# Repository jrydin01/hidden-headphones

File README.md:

# Hidden Headphones

> **Bone conduction headphones that sit on your collarbone, completely hidden under your shirt.**

Hidden Headphones is an open-source hardware project for a discrete, neckband-style bone conduction audio device. The electronics sit in a small rear enclosure while flexible wiring runs through the neckband to vibration pads positioned on the collarbone. The goal is a hands-free listening device that can be worn beneath a shirt.

This repository contains the design documentation, KiCad source files, firmware, bill of materials, and OpenSCAD enclosure model for the current prototype revision.

---

## Overview & Architecture

The audio path begins with a phone or computer sending Bluetooth Classic A2DP audio to the original ESP32. The microcontroller outputs stereo PCM audio over I2S to the PCM5102A DAC. Two PAM8302A mono amplifiers drive the left and right bone conduction transducers installed in sealed TPU contact pads.

The project utilizes a custom electronics assembly, dedicated power subsystem, and 3D-printed housing:

* **Core processor:** Original ESP32-WROOM-32 development board with Wi-Fi and Bluetooth Classic
* **Audio input:** Bluetooth A2DP sink running on the ESP32
* **Audio conversion:** PCM5102A stereo I2S DAC
* **Amplification:** Two PAM8302A 2.5 W class-D mono amplifier boards
* **Transducers:** Two 8 ohm, 1 W bone conduction transducers
* **Power:** 3.7 V, 1000 mAh LiPo battery and USB-C TP4056 charging/protection module
* **Controls:** Active-low tactile volume buttons with internal pull-ups
* **Housing:** PETG rear electronics box with flexible TPU neckband sections and sealed contact pads

### Audio and control pins

The current firmware uses the following original ESP32 GPIO assignments:

| Function | GPIO | Notes |
| --- | ---: | --- |
| I2S LRCK / word select | 25 | PCM5102A clock signal |
| I2S BCK / bit clock | 26 | PCM5102A clock signal |
| I2S data out | 22 | PCM5102A serial audio data |
| Volume up | 16 | Active LOW, SW1 |
| Volume down | 17 | Active LOW, SW2 |
| Play/pause | 18 | Active LOW, SW3 |
| Status LED | 19 | LED_STATUS output |

The buttons use a 50 ms software debounce interval. A press changes the Bluetooth sink volume by 10 steps, clamped to the supported range of 0 to 127. The device advertises as **Hidden Headphones**.

## Features

* Hidden collarbone-mounted bone conduction audio
* Wireless Bluetooth A2DP playback
* Stereo output through two independent transducers
* USB-C charging through the TP4056 module
* Dedicated volume up and volume down controls
* Modular rear electronics enclosure
* Flexible cable routing through the neckband
* Open KiCad schematic and PCB source files
* Parametric OpenSCAD enclosure source

## Bill of materials

The complete sourcing list is available in [BOM.csv](BOM.csv). The main assemblies are:

| Category | Part | Quantity |
| --- | --- | ---: |
| Microcontroller | ESP32-WROOM-32 development board | 1 |
| Audio DAC | PCM5102A I2S stereo module | 1 |
| Amplifier | PAM8302A mono amplifier board | 2 |
| Power management | USB-C TP4056 charging and protection module | 1 |
| Battery | 3.7 V 1000 mAh LiPo pack | 1 |
| Audio | Bone conduction transducer, 8 ohm / 1 W | 2 |
| Controls | 6 x 6 x 5 mm tactile push buttons | 3 |
| Hardware | M2 brass heat-set inserts | 4 |
| Wiring | 28 AWG stranded silicone wire | 1 set |
| Printed materials | TPU and PETG filament | 1 spool each |

## Hardware design

The first design phase established the collarbone contact-pad concept, rear electronics box, battery position, and cable route. The second revision reorganized the electronics around dual amplifier channels and added space for the updated power and audio circuitry.

The rear enclosure is modeled in [rear_box.scad](rear_box.scad). Its current design includes:

* A hollow electronics cavity measuring 55 x 30 x 18 mm internally
* A 2 mm nominal wall thickness
* A USB-C charging-port cutout
* Left and right conduit openings for the neckband wiring
* Four internal PCB mounting posts
* M2 screw and heat-set insert locations
* Separate bottom-case and lid modules for 3D printing

The neckband is intended to use flexible TPU sections for comfort and PETG for the more rigid rear enclosure. The contact pads are designed around sealed TPU housings, with cable strain relief and acoustic tuning features considered in the mechanical revision.

## Firmware

The source firmware is available in [firmware.ino](firmware.ino). It uses the Arduino framework and `ESP32-A2DP` to receive Bluetooth audio and route it over I2S to the PCM5102A and PAM8302A amplifiers. It also handles the three active-low controls and status LED shown in the design diagram.

The firmware currently:

1. Starts a Bluetooth A2DP sink named `Hidden Headphones`.
2. Configures the ESP32 I2S output for the PCM5102A.
3. Enables internal pull-ups for the volume and play/pause buttons.
4. Debounces button input and applies software volume scaling.
5. Controls A2DP playback and the status LED with the play/pause button.
6. Reports startup and control changes over the serial monitor at 115200 baud.

The root-level [firmware.ino](firmware.ino) is also retained as a firmware source snapshot. Keep the two copies synchronized when making firmware changes.

### Flashing and verification

1. Install the ESP32 Arduino board support package and the `ESP32-A2DP` library.
2. Select an original ESP32/WROOM-32 board and its USB serial port.
3. Flash `firmware.ino`.
4. Open a serial monitor at 115200 baud.
6. Confirm the `Bluetooth A2DP sink and PCM5102A I2S output ready` message.
7. Pair a phone or computer with **Hidden Headphones** and verify stereo audio, volume, and play/pause controls.

The pin assignments should be checked against the revised PCB before powering the complete system. The selected GPIOs avoid GPIO0 boot strapping and GPIO1 serial TX conflicts on the ESP32-WROOM-32. The PCB must match this mapping before flashing the firmware.

## Repository structure

```text
.
├── BOM.csv                                      # Component list and sourcing links
├── JOURNAL.md                                   # Project development log and time tracking
├── LICENSE                                      # CC0-1.0 license
├── README.md                                    # Project overview and build guide
├── firmware.ino                                 # Root firmware snapshot
├── firmware.ino                                 # ESP32 Bluetooth A2DP firmware
├── rear_box.scad                                # Parametric rear enclosure model
├── Hidden_Headphones_All_Components_v3.kicad_sch # KiCad schematic
├── Hidden_Headphones_All_Components_v3.kicad_pcb # KiCad PCB layout
├── Hidden_Headphones_All_Components_v3.kicad_pro # KiCad project settings
├── images/                                      # Design, CAD, PCB, and firmware images
└── Untitled/                                    # Additional KiCad working files
```

## Project history

The development log in [JOURNAL.md](JOURNAL.md) records the design process and time spent on each stage:

* **Initial concept:** Established the ESP32 audio architecture, collarbone contact pads, TPU housing, and USB-C rechargeable battery system.
* **CAD and assembly:** Designed the rear electronics box, internal mounting layout, cable conduits, and labyrinth-style strain relief.
* **Component sourcing:** Selected the controller, DAC, amplifiers, charging module, battery, transducers, controls, hardware, wiring, and print materials.
* **Architecture revision:** Added dual PAM8302A amplifiers, revised the power system, and documented the antenna keep-out and sealed contact-pad concepts.
* **Housing model:** Completed the main swept and hollowed enclosure and aligned internal hardware mounting points.
* **PCB design:** Created the KiCad schematic and board layout, resolved schematic and footprint issues, and prepared the design for fabrication.
* **Firmware:** Implemented Bluetooth A2DP playback, I2S routing, volume controls, debouncing, serial output, and the flashing verification procedure.

## Current status

The repository represents a prototype design prepared for hardware fabrication and bring-up. The PCB, firmware, and enclosure should be validated together on assembled hardware, especially the power connections, GPIO assignments, amplifier wiring, battery protection, enclosure clearances, and transducer sealing.

This is an experimental hardware project. Use an appropriate LiPo charging module, inspect batteries and wiring for damage, and do not leave the device charging unattended.

---

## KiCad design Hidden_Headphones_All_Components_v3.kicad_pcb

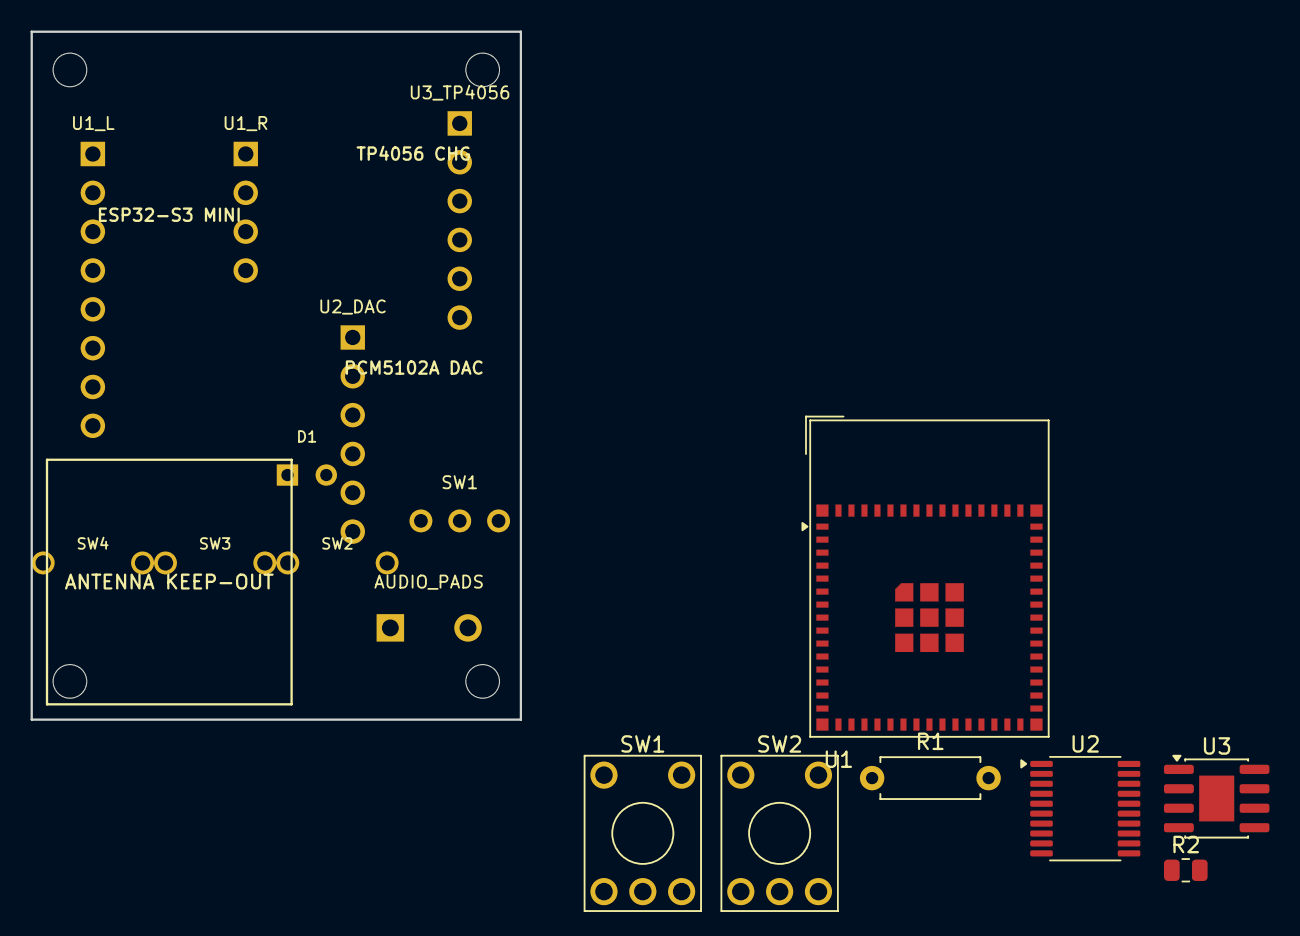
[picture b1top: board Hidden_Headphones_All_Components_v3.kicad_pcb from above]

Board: 2 copper layers, 32.0 x 45.0 mm, 17 parts (0 on the bottom side), 20 nets, no tracks yet.

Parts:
AUDIO_PADS: AUDIO; TerminalBlock_bornier-2_P5.08mm
D1: STATUS; LED_D3.0mm
R1: 1.2kΩ; R_Axial_DIN0207_L6.3mm_D2.5mm_P7.62mm_Horizontal
R2: 10kΩ; R_0805_2012Metric
SW1: POWER; SW_Slide_SPDT_EG1218
SW1#2, SW2: SW_Push; KSA_Tactile_SPST
SW2#2: VOL+; SW_PUSH_6mm
SW3: VOL-; SW_PUSH_6mm
SW4: PLAY; SW_PUSH_6mm
U1: ESP32-S3-MINI-1; ESP32-S2-MINI-1
U1_L: ESP32_L; PinHeader_1x08_P2.54mm_Vertical
U1_R: ESP32_R; PinHeader_1x04_P2.54mm_Vertical
U2: PCM5102A; TSSOP-20_4.4x6.5mm_P0.65mm
U2_DAC: PCM5102A; PinHeader_1x06_P2.54mm_Vertical
U3: TP4056-42-ESOP8; SOIC-8-1EP_3.9x4.9mm_P1.27mm_EP2.29x3mm
U3_TP4056: TP4056; PinHeader_1x06_P2.54mm_Vertical

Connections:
+3V3_PWR: SW1.2, U1_L.1, U1_R.3, U2_DAC.1, U3_TP4056.5
BTN_PLAY_PAUSE: SW4.1, U1_L.8
BTN_VOL_DOWN: SW3.1, U1_L.7
BTN_VOL_UP: SW2#2.1, U1_L.6
GND: D1.2, SW2#2.2, SW3.2, SW4.2, U1_L.2, U1_R.2, U1_R.4, U2_DAC.2, U2_DAC.6, U3_TP4056.2, U3_TP4056.4, U3_TP4056.6
I2S_BCK: U1_L.4, U2_DAC.4
I2S_DATA: U1_L.5, U2_DAC.5
I2S_LRCK: U1_L.3, U2_DAC.3
LED_STATUS: D1.1, U1_R.1
unnamed: SW1#2.2, SW2.2, U1.1 (GND), U1.2 (GND), U1.42 (GND), U1.43 (GND), U1.46 (GND), U1.47 (GND), U1.48 (GND), U1.49 (GND), U1.50 (GND), U1.51 (GND), U1.52 (GND), U1.53 (GND), U1.54 (GND), U1.55 (GND), U1.56 (GND), U1.57 (GND), U1.58 (GND), U1.59 (GND), U1.60 (GND), U1.61 (GND), U1.62 (GND), U1.63 (GND), U1.64 (GND), U1.65 (GND)
unnamed: R2.2, U1.3 (3V3), U2.1 (CPVDD), U2.8 (AVDD), U2.17 (XSMT), U2.20 (DVDD)
unnamed: R2.1, U1.45 (EN)
unnamed: SW1#2.1, U1.4 (IO0)
unnamed: SW2.1, U1.5 (IO1), U2.14 (DIN)
unnamed: U1.25 (IO21), U2.15 (LRCK)
unnamed: U1.26 (IO26), U2.13 (BCK)
unnamed: R1.2, U2.3 (CPGND), U2.9 (AGND), U2.10 (DEMP), U2.11 (FLT), U2.12 (SCK), U2.16 (FMT), U2.19 (DGND), U3.3 (GND), U3.9 (EPAD)
unnamed: U3.4 (V_{CC}), U3.8 (CE)
unnamed: R1.1, U3.2 (PROG)
VBAT: SW1.1, U3_TP4056.3

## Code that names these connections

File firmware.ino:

/*
 * Hidden Headphones - ESP32 Bluetooth A2DP firmware
 *
 * This sketch targets an original ESP32/WROOM-32 board. Unlike the ESP32-S3,
 * the original ESP32 supports Bluetooth Classic A2DP for phone audio.
 */

#include <Arduino.h>
#include <BluetoothA2DPSink.h>
#include <driver/i2s.h>

// I2S connection to the PCM5102A.
constexpr gpio_num_t I2S_BCK_PIN = GPIO_NUM_26;
constexpr gpio_num_t I2S_LRCK_PIN = GPIO_NUM_25;
constexpr gpio_num_t I2S_DATA_PIN = GPIO_NUM_22;

// Active-low controls from the diagram. Keep these separate from I2S pins.
constexpr gpio_num_t BTN_VOL_UP = GPIO_NUM_16;
constexpr gpio_num_t BTN_VOL_DOWN = GPIO_NUM_17;
constexpr gpio_num_t BTN_PLAY_PAUSE = GPIO_NUM_18;
constexpr gpio_num_t LED_STATUS = GPIO_NUM_19;

constexpr uint32_t BUTTON_DEBOUNCE_MS = 50;
constexpr int16_t VOLUME_STEP = 10;
constexpr int16_t MAX_VOLUME = 127;

BluetoothA2DPSink a2dpSink;

struct Button {
  gpio_num_t pin;
  bool lastReading;
  bool stableState;
  uint32_t lastChangeMs;
  void (*onPress)();
};

int16_t volume = 64;
bool playing = true;

void onVolumeUp();
void onVolumeDown();
void onPlayPause();

Button buttons[] = {
    {BTN_VOL_UP, HIGH, HIGH, 0, onVolumeUp},
    {BTN_VOL_DOWN, HIGH, HIGH, 0, onVolumeDown},
    {BTN_PLAY_PAUSE, HIGH, HIGH, 0, onPlayPause},
};

void configureI2S() {
  i2s_pin_config_t pins = {};
  pins.bck_io_num = I2S_BCK_PIN;
  pins.ws_io_num = I2S_LRCK_PIN;
  pins.data_out_num = I2S_DATA_PIN;
  pins.data_in_num = I2S_PIN_NO_CHANGE;
  a2dpSink.set_pin_config(pins);
}

void handleButton(Button &button) {
  const bool reading = digitalRead(button.pin);
  const uint32_t now = millis();

  if (reading != button.lastReading) {
    button.lastChangeMs = now;
    button.lastReading = reading;
  }

  if (now - button.lastChangeMs >= BUTTON_DEBOUNCE_MS && reading != button.stableState) {
    button.stableState = reading;
    if (button.stableState == LOW) {
      button.onPress();
    }
  }
}

void onVolumeUp() {
  volume = min<int16_t>(MAX_VOLUME, a2dpSink.get_volume() + VOLUME_STEP);
  a2dpSink.set_volume(volume);
  Serial.printf("Volume UP: %d/127\n", volume);
}

void onVolumeDown() {
  volume = max<int16_t>(0, a2dpSink.get_volume() - VOLUME_STEP);
  a2dpSink.set_volume(volume);
  Serial.printf("Volume DOWN: %d/127\n", volume);
}

void onPlayPause() {
  playing = !playing;
  if (playing) {
    a2dpSink.play();
  } else {
    a2dpSink.pause();
  }
  digitalWrite(LED_STATUS, playing ? HIGH : LOW);
  Serial.printf("Playback %s\n", playing ? "started" : "paused");
}

void setup() {
  Serial.begin(115200);
  delay(200);
  Serial.println("Starting Hidden Headphones ESP32 Bluetooth A2DP firmware");

  pinMode(LED_STATUS, OUTPUT);
  digitalWrite(LED_STATUS, HIGH);
  for (Button &button : buttons) {
    pinMode(button.pin, INPUT_PULLUP);
  }

  configureI2S();
  a2dpSink.start("Hidden Headphones");
  a2dpSink.set_volume(volume);
  Serial.println("Bluetooth A2DP sink and PCM5102A I2S output ready");
}

void loop() {
  for (Button &button : buttons) {
    handleButton(button);
  }
}
